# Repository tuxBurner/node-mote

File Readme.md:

# Node - Mote

Still under development.

## Pi Notes

Turn Display on and off:

echo 0 > /sys/class/backlight/rpi_backlight/bl_power

echo 1 > /sys/class/backlight/rpi_backlight/bl_power

Set Brightness value goes from 0 to 255

echo 50 > /sys/class/backlight/rpi_backlight/brightness

### Display rotation

Rotates the touchscreen 180 degree and the input

lcd_rotate=2

Rotates the screen 90 degree

display_rotate=1

call this to get the input remapped 

xinput --set-prop 'FT5406 memory based driver' 'Coordinate Transformation Matrix'  0 1 0 -1 0 1 0 0 1

## Hide the mousecursor

```bash
sudo apt-get install unclutter
```

## Start chromium in kiosk mode

```bash
DISPLAY=:0 chromium-browser --disable-infobars --kiosk --disable-pinch  --incognito --disable-overlay-scrollbar --touch-events http://192.168.0.2:3000
```

## Lirc on the pi

```bash
sudo apt-get install lirc
```

## Links

### Pi Rotate screen

* https://www.raspberrypi.org/forums/viewtopic.php?t=120793

### Pi Kioskmode
* http://www.lukebrowning.com/hardware/raspberry-pi/touch-screen-chromium-kiosk-on-the-raspberry-pi/
* https://itrig.de/index.php?/archives/2309-Raspberry-Pi-3-Kiosk-Chromium-Autostart-im-Vollbildmodus-einrichten.html
* https://forum.fhem.de/index.php?topic=51180.0

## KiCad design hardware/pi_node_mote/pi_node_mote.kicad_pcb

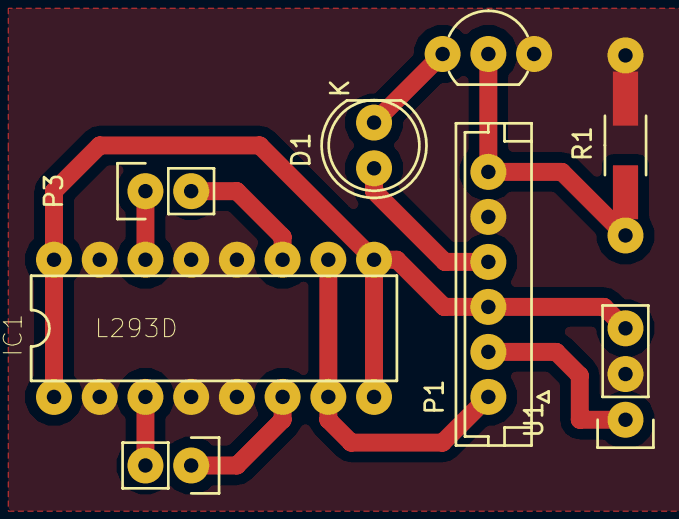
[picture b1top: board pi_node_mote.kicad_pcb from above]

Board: 2 copper layers, 8 parts (0 on the bottom side), 11 nets.

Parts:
D1: LED; LED-5MM
IC1: L293D; DIL16
P1: CONN_01X06; JST_EH_B06B-EH-A_06x2.50mm_Straight
P2: CONN_01X02; Socket_Strip_Straight_1x02
P3: CONN_01X02; Pin_Header_Straight_1x02
Q1: BS170; TO-92_Inline_Wide
R1: R; Resistor_SMD+THTuniversal_1206_RM10_HandSoldering
U1: TSOP38238; Socket_Strip_Straight_1x03

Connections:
+3V3: IC1.1, IC1.8, IC1.9, IC1.16, P1.3, U1.3
+5V: D1.2, P1.4
GND: IC1.2, IC1.4, IC1.5, IC1.12, IC1.13, IC1.15, P1.5, Q1.3, R1.2, U1.2
unnamed: D1.1, Q1.1
unnamed: IC1.3, P2.2
unnamed: IC1.6, P2.1
unnamed: IC1.7, IC1.10, P1.1
unnamed: IC1.11, P3.2
unnamed: IC1.14, P3.1
unnamed: P1.2, U1.1
unnamed: P1.6, Q1.2, R1.1

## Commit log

2017-07-24 Better Panel handling
2017-07-24 Slider works now
2017-07-24 Slider step size
2017-07-26 Add a switch for toggling mute state
2017-07-26 Start adding swipe
2017-07-27 Made the swipe work
2017-07-31 Added a pcb
2017-07-31 Tapping
2017-07-31 Deleted zip
2017-07-31 Added gcode
2017-08-01 Deeper cutting
2017-08-01 2 passes in gcode
2017-08-14 State change of a backend is pushed to the frontend now
2017-08-14 Total rewrite of the gui component creation
2017-08-14 First attemp for handling backend data change
2017-08-18 Start adding firetv support
2017-08-18 Add firetv support
2017-08-19 Clicking on the backend link in the menu does no something :)
2017-08-20 Lirc added
2017-08-21 Start to add denon avr client
2017-08-21 Make denon panels better
2017-09-08 Some rework with the states
2017-09-08 New Backend docs
2017-09-08 Some doc and started adding activities
2017-09-14 Activity panels are now loading
2017-09-14 Vibrate on every event
2017-09-14 Some minor GUI changes
2017-09-15 Mark the currenst state active in the menu
2017-09-19 Status for activity started to implement
2017-09-19 Start to refactor gui code to a class based component system
2017-09-20 Some changes in the Gui components
2017-09-25 Event handling in the components now
2017-09-25 Select component added
2017-09-26 Select is now updating and denon is working better now
2017-09-27 Activity code
2017-09-27 Activity is working now
2017-09-27 Backends === Devices
2017-10-07 Add a tiny favicon
2017-10-08 Add manifest.json
2017-10-09 Start to put everything in gui components
2017-11-16 Add some links and pi infos
2017-11-16 Minor changes
2017-11-16 Fix Buttons to big on small screens
2017-11-16 Start to add xbmc player panel
2017-11-16 Add new label text component
2017-11-17 Dont fail on undefined
2018-05-11 Library lifts
2018-05-11 Add swipe press action
2018-05-11 Stuff
2019-06-21 Added lirc
